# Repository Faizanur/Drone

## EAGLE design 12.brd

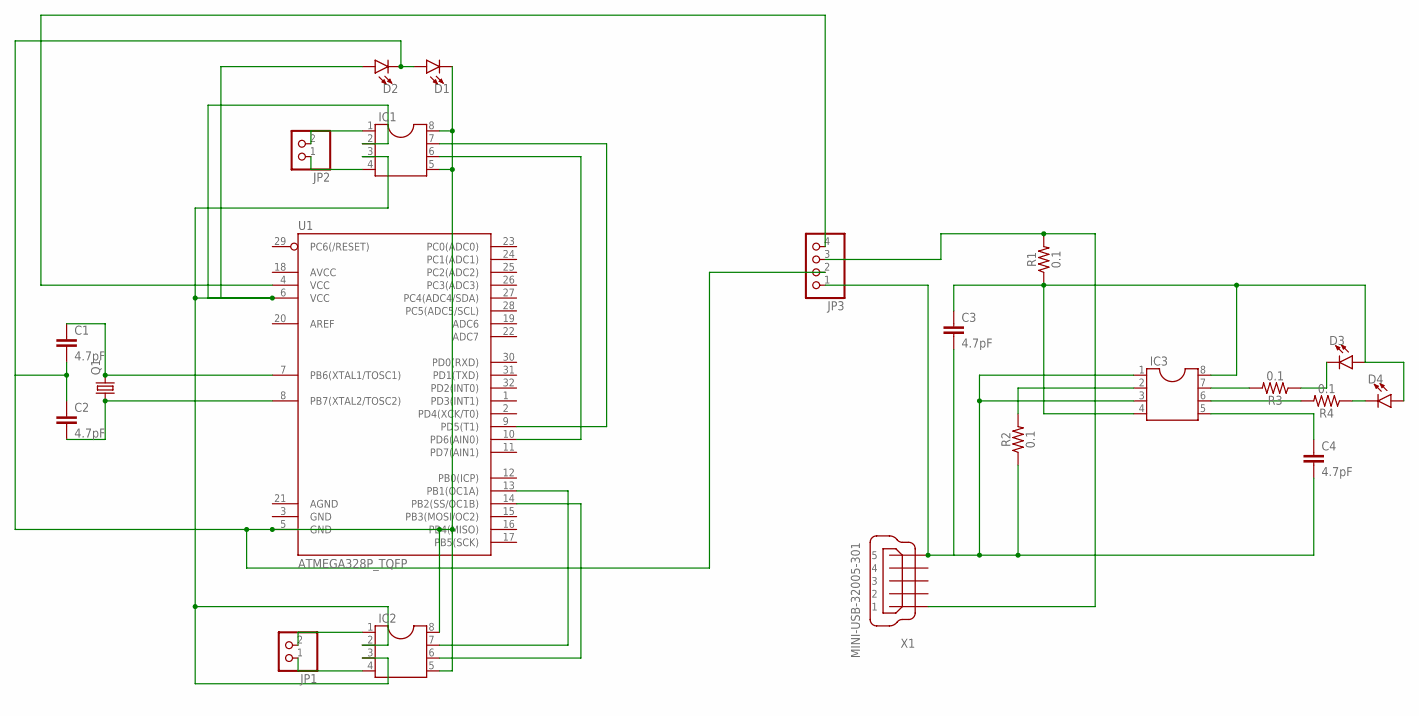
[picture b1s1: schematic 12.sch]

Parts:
C1, C2, C3, C4: 4.7pF; 0603
D1, D2, D3, D4: LED0603; LED-0603
IC1, IC2, IC3: DIL8; DIL08
JP1, JP2: PINHD-1X2; 1X02
JP3: PINHD-1X4; 1X04
Q1: CRYSTALHC49UP; HC49UP
R1, R2, R3, R4: 0.1; 1210
U1: ATMEGA328P_TQFP; TQFP32-08
X1: MINI-USB-32005-301; 32005-301

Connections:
unnamed: JP3.4, U1.4 (VCC)
unnamed: D2.A, IC1.2, IC1.3, IC2.2, IC2.3, U1.6 (VCC)
unnamed: IC1.1, JP2.2
unnamed: IC1.6, U1.10 (PD6(AIN0))
unnamed: IC1.7, U1.9 (PD5(T1))
unnamed: IC2.7, U1.13 (PB1(OC1A))
unnamed: IC2.6, U1.14 (PB2(SS/OC1B))
unnamed: C1.1, Q1.2, U1.7 (PB6(XTAL1/TOSC1))
unnamed: C2.2, Q1.1, U1.8 (PB7(XTAL2/TOSC2))
unnamed: IC1.4, JP2.1
unnamed: IC2.1, JP1.2
unnamed: IC2.4, JP1.1
unnamed: C3.1, D3.A, D4.A, IC3.4, IC3.8, R1.1
unnamed: IC3.7, R3.2
unnamed: IC3.6, R4.2
unnamed: D3.C, R3.1
unnamed: D4.C, R4.1
unnamed: C4.1, IC3.5
unnamed: C1.2, C2.1, D1.A, D1.C, D2.C, IC1.5, IC1.8, IC2.5, IC2.8, JP3.2, U1.5 (GND)
unnamed: IC3.2, R2.2
unnamed: C3.2, C4.2, IC3.1, IC3.3, JP3.1, R2.1, X1.5
unnamed: JP3.3, R1.2, X1.1

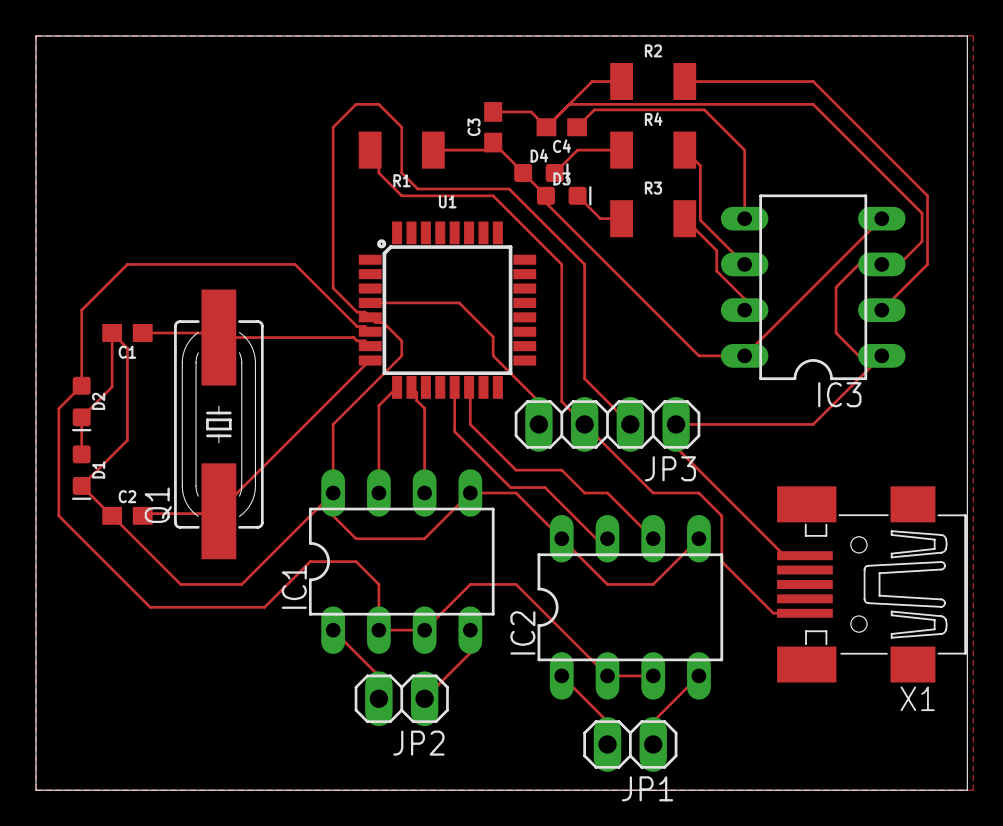
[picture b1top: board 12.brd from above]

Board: 2 copper layers, 51.7 x 41.9 mm, 21 parts (0 on the bottom side), 22 nets.

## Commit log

2022-07-04 sahil added
2022-07-04 Refurbished
2022-07-04 12 added

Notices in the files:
parts and their libraries:
SparkFun-Capacitors: Licensing: Creative Commons ShareAlike 4.0 International - https://creativecommons.org/licenses/by-sa/4.0
